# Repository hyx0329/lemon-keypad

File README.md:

# Lemon Keypad

> [English](README.md), [简体中文](README.zh.md)

A macro pad/mechanical keyboard based on RP2040. This is *probably* an *improved* version of the [original adafruit version](https://learn.adafruit.com/qtpy-lemon-mechanical-keypad-macropad/).

This is a simple 6-key keypad. What makes it different is that the main program is written in async Python(CircuitPython).
With python's flexibility, a lot can be done with ease with this keypad, on demand.

<!-- TOC depthfrom:2 -->

- [Project folders and their content](#project-folders-and-their-content)
- [Software implementation](#software-implementation)
    - [implemented](#implemented)
    - [potentials left to users](#potentials-left-to-users)
- [Hardware components](#hardware-components)
- [The real thing: close looks](#the-real-thing-close-looks)

<!-- /TOC -->

This repo consists of shell CAD(FreeCAD & STL), PCB design files(KiCAD), and software(CircuitPython project).

I found myself lack the capability/motivation to productize it, so I decided to publish it and hope it last longer, inspiring others.

## Project folders and their content

- CAD: stores CAD files for shell
- lemon-rp2040-keypad: kicad project file
- software: CircuitPython project directory

## Software implementation

### implemented

- keyboard keys input
    - including consumer control keys
- mouse input
- complex key actions
    - key combinations
    - key sequences
    - tap dance
    - layer switch
    - delay
- custom function
    - gyro mouse(built-in example)
    - level gauge(built-in example)

### potentials left to users

- random number generator
- Whack-a-Mole
- a BIG button used up-side-down
- password storage(with pin protection)
- ducky pad
- etc.

## Hardware components

- RP2040
- LSM6DS3TRC inertial module(gyro & accelerometer)
- WS2812 * 6
- MX switch hot-swappable socket
- Kailh BOX white switches
- WB25Q128JVSQ flash memory
- AMS1117-3V3
- misc passive components

## The real thing: close looks

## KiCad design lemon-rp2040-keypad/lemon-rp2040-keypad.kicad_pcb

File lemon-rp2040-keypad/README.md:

# Lemmon Keypad KiCAD Project

Have fun! :D It's just a prototype and design issues may exist, despite I did verify the design with the real thing.

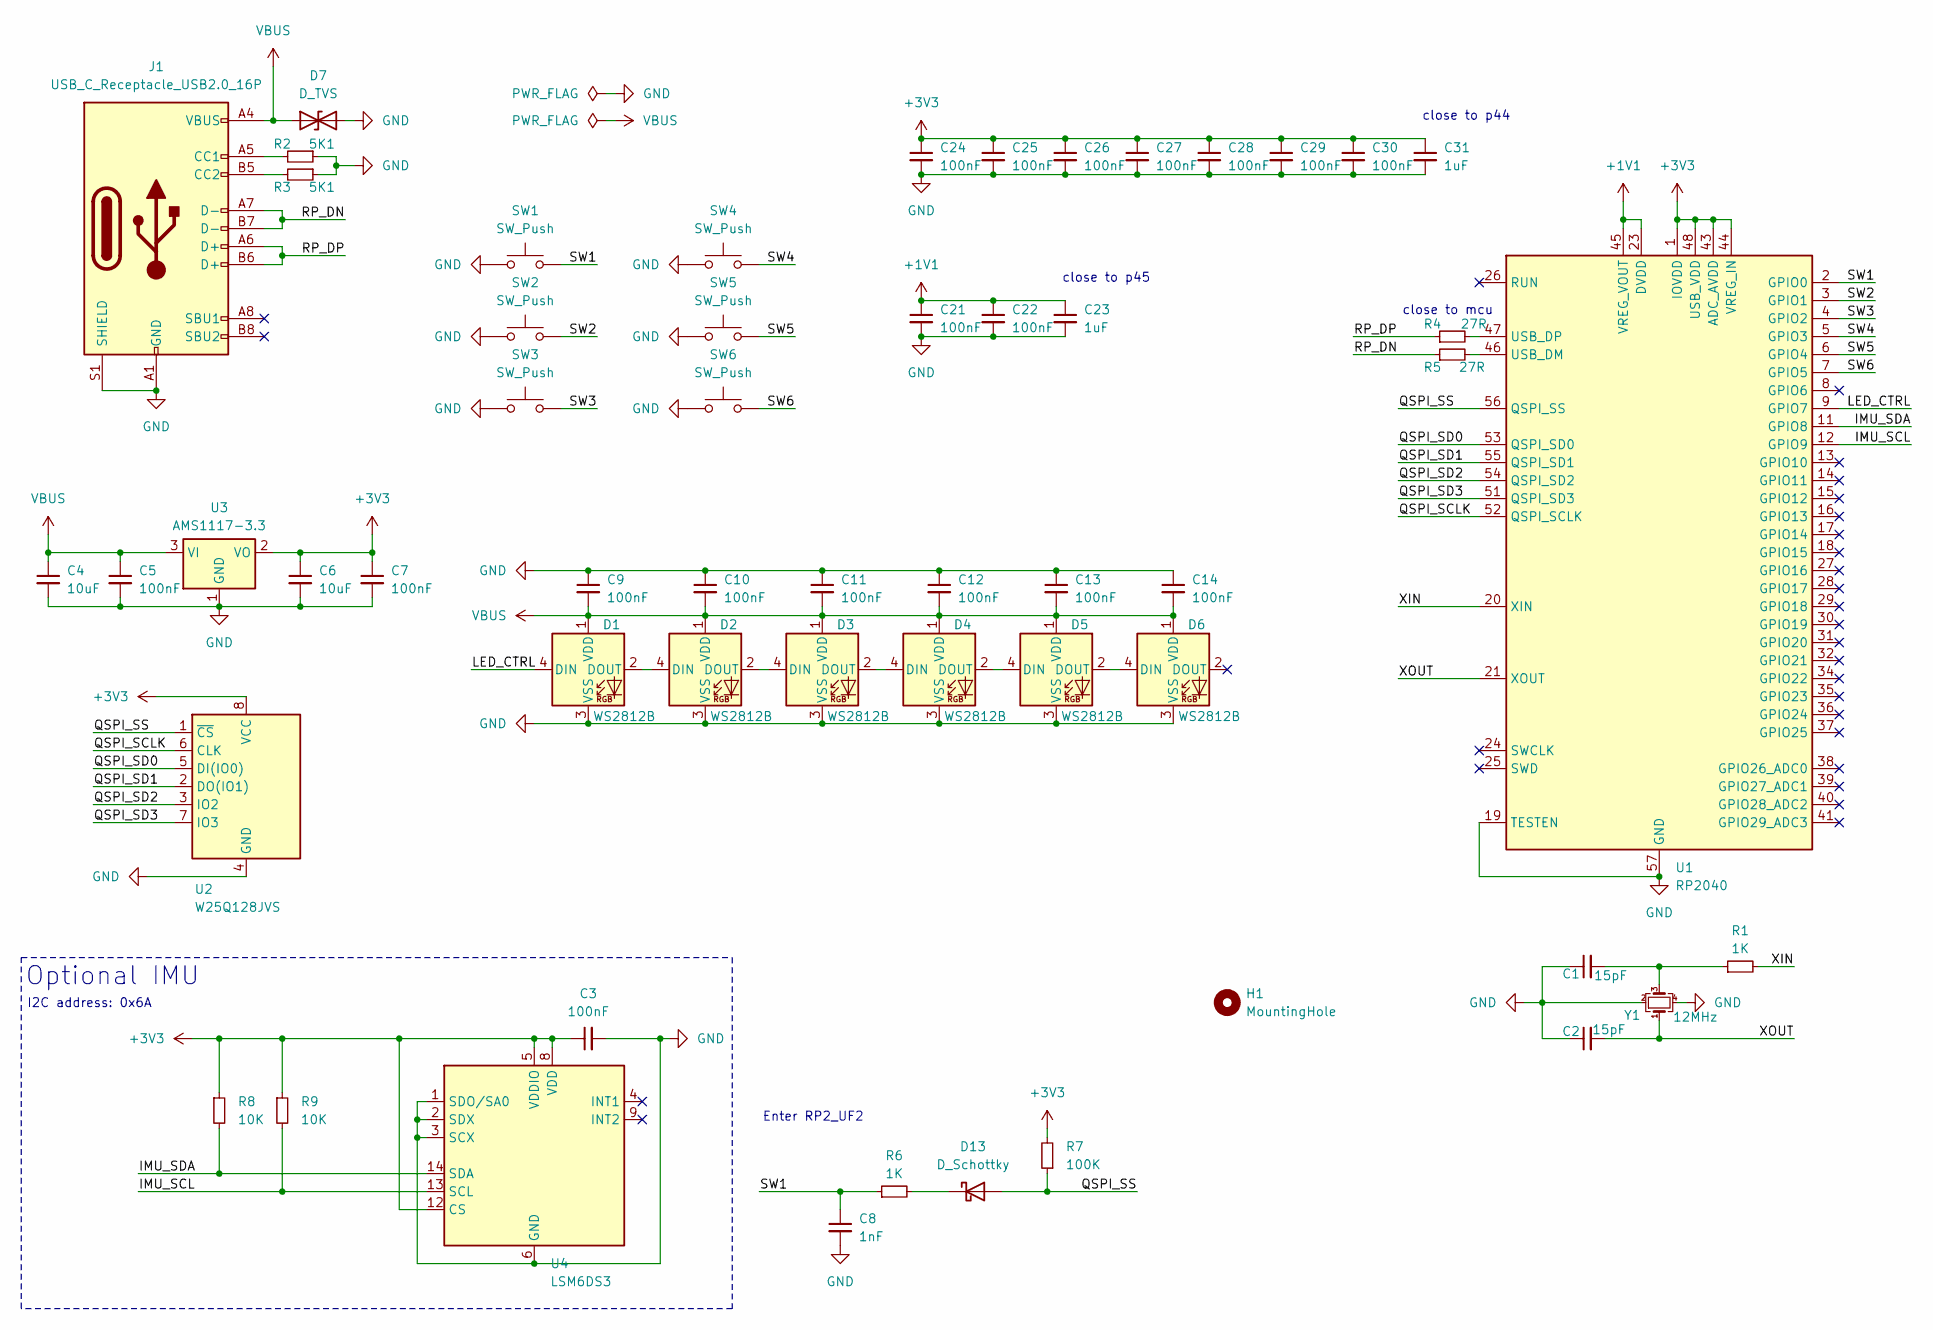
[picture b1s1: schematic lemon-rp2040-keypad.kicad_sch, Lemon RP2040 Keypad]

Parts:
C1, C2: 15pF; C_0402_1005Metric
C3, C5, C7, C9, C10, C11, C12, C13, C14, C21, C22, C24, C25, C26, C27, C28, C29, C30: 100nF; C_0402_1005Metric
C4, C6: 10uF; C_0603_1608Metric
C8: 1nF; C_0402_1005Metric
C23, C31: 1uF; C_0402_1005Metric
D1, D2, D3, D4, D5, D6: WS2812B; LED_WS2812B_PLCC4_5.0x5.0mm_P3.2mm
D7: D_TVS; D_SOD-323
D13: D_Schottky; D_SOD-323
H1: MountingHole; MountingHole_3.2mm_M3
J1: USB_C_Receptacle_USB2.0_16P; USB_C_Receptacle_G-Switch_GT-USB-7010ASV
R1, R6: 1K; R_0402_1005Metric
R2, R3: 5K1; R_0402_1005Metric
R4, R5: 27R; R_0402_1005Metric
R7: 100K; R_0402_1005Metric
R8, R9: 10K; R_0402_1005Metric
SW1, SW2, SW3, SW4, SW5, SW6: SW_Push; Kailh_socket_MX_optional
U1: RP2040; QFN-56-1EP_7x7mm_P0.4mm_EP3.2x3.2mm
U2: W25Q128JVS; SOIC-8_5.23x5.23mm_P1.27mm
U3: AMS1117-3.3; SOT-223-3_TabPin2
U4: LSM6DS3; LGA-14_3x2.5mm_P0.5mm_LayoutBorder3x4y
Y1: 12MHz; Crystal_SMD_3225-4Pin_3.2x2.5mm

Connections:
+1V1: C21.1, C22.1, C23.1, U1.23 (DVDD), U1.45 (VREG_VOUT), U1.50 (DVDD)
+3V3: C3.1, C6.1, C7.1, C24.1, C25.1, C26.1, C27.1, C28.1, C29.1, C30.1, C31.1, R7.2, R8.1, R9.1, U1.1 (IOVDD), U1.10 (IOVDD), U1.22 (IOVDD), U1.33 (IOVDD), U1.42 (IOVDD), U1.43 (ADC_AVDD), U1.44 (VREG_IN), U1.48 (USB_VDD), U1.49 (IOVDD), U2.8 (VCC), U3.2 (VO), U4.5 (VDDIO), U4.8 (VDD), U4.12 (CS)
/IMU_SCL: R9.2, U1.12 (GPIO9), U4.13 (SCL)
/IMU_SDA: R8.2, U1.11 (GPIO8), U4.14 (SDA)
/LED_CTRL: D1.4 (DIN), U1.9 (GPIO7)
/QSPI_SCLK: U1.52 (QSPI_SCLK), U2.6 (CLK)
/QSPI_SD0: U1.53 (QSPI_SD0), U2.5 (DI(IO0))
/QSPI_SD1: U1.55 (QSPI_SD1), U2.2 (DO(IO1))
/QSPI_SD2: U1.54 (QSPI_SD2), U2.3 (IO2)
/QSPI_SD3: U1.51 (QSPI_SD3), U2.7 (IO3)
/QSPI_SS: D13.2 (A), R7.1, U1.56 (QSPI_SS), U2.1 (~CS)
/RP_DN: J1.A7 (D-), J1.B7 (D-), R5.1
/RP_DP: J1.A6 (D+), J1.B6 (D+), R4.1
/SW1: C8.1, R6.1, SW1.1, U1.2 (GPIO0)
/SW2: SW2.2, U1.3 (GPIO1)
/SW3: SW3.2, U1.4 (GPIO2)
/SW4: SW4.2, U1.5 (GPIO3)
/SW5: SW5.2, U1.6 (GPIO4)
/SW6: SW6.2, U1.7 (GPIO5)
/XIN: R1.2, U1.20 (XIN)
/XOUT: C2.2, U1.21 (XOUT), Y1.1
GND: C1.1, C2.1, C3.2, C4.2, C5.2, C6.2, C7.2, C8.2, C9.1, C10.1, C11.1, C12.1, C13.1, C14.1, C21.2, C22.2, C23.2, C24.2, C25.2, C26.2, C27.2, C28.2, C29.2, C30.2, C31.2, D1.3 (VSS), D2.3 (VSS), D3.3 (VSS), D4.3 (VSS), D5.3 (VSS), D6.3 (VSS), D7.2 (A2), J1.A1 (GND), J1.A12 (GND), J1.B1 (GND), J1.B12 (GND), J1.S1 (SHIELD), R2.1, R3.1, SW1.2, SW2.1, SW3.1, SW4.1, SW5.1, SW6.1, U1.19 (TESTEN), U1.57 (GND), U2.4 (GND), U3.1 (GND), U4.1 (SDO/SA0), U4.2 (SDX), U4.3 (SCX), U4.6 (GND), U4.7 (GND), Y1.2, Y1.4
unnamed: C1.2, R1.1, Y1.3
unnamed: D1.2 (DOUT), D2.4 (DIN)
unnamed: D2.2 (DOUT), D3.4 (DIN)
unnamed: D3.2 (DOUT), D4.4 (DIN)
unnamed: D4.2 (DOUT), D5.4 (DIN)
unnamed: D5.2 (DOUT), D6.4 (DIN)
unnamed: D13.1 (K), R6.2
unnamed: J1.A5 (CC1), R2.2
unnamed: J1.B5 (CC2), R3.2
unnamed: R5.2, U1.46 (USB_DM)
unnamed: R4.2, U1.47 (USB_DP)
VBUS: C4.1, C5.1, C9.2, C10.2, C11.2, C12.2, C13.2, C14.2, D1.1 (VDD), D2.1 (VDD), D3.1 (VDD), D4.1 (VDD), D5.1 (VDD), D6.1 (VDD), D7.1 (A1), J1.A4 (VBUS), J1.A9 (VBUS), J1.B4 (VBUS), J1.B9 (VBUS), U3.3 (VI)

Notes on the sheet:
Enter RP2_UF2
close to mcu
I2C address: 0x6A
close to p45
Optional IMU
close to p44

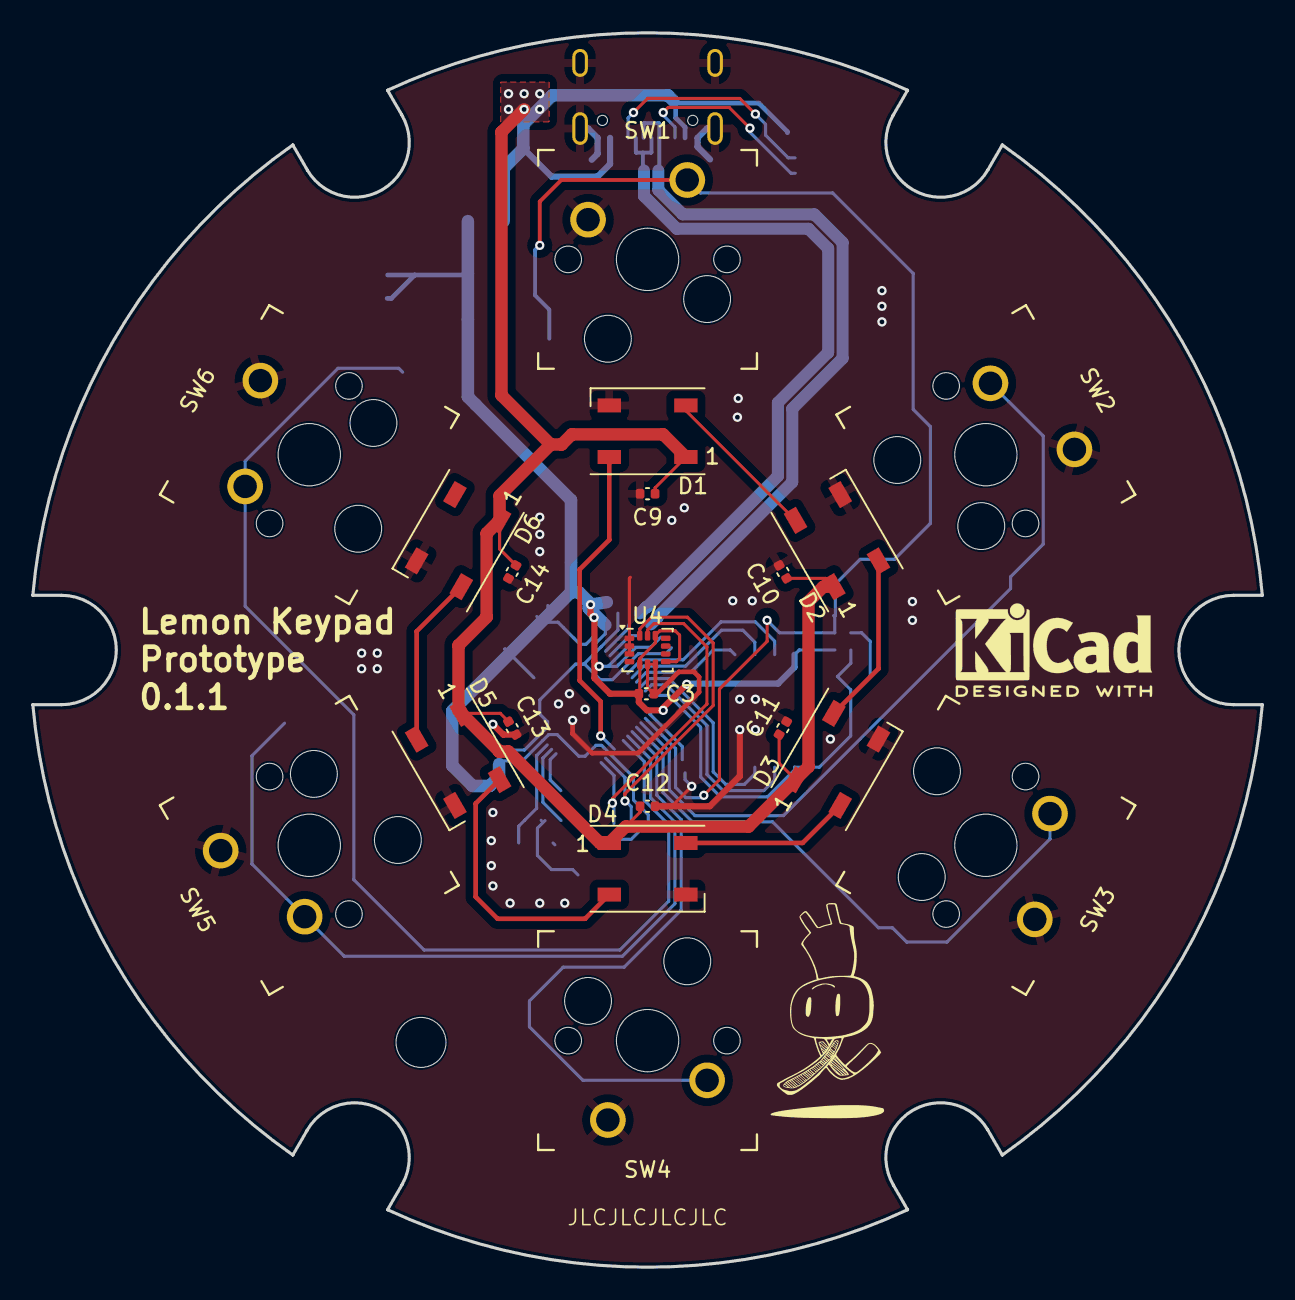
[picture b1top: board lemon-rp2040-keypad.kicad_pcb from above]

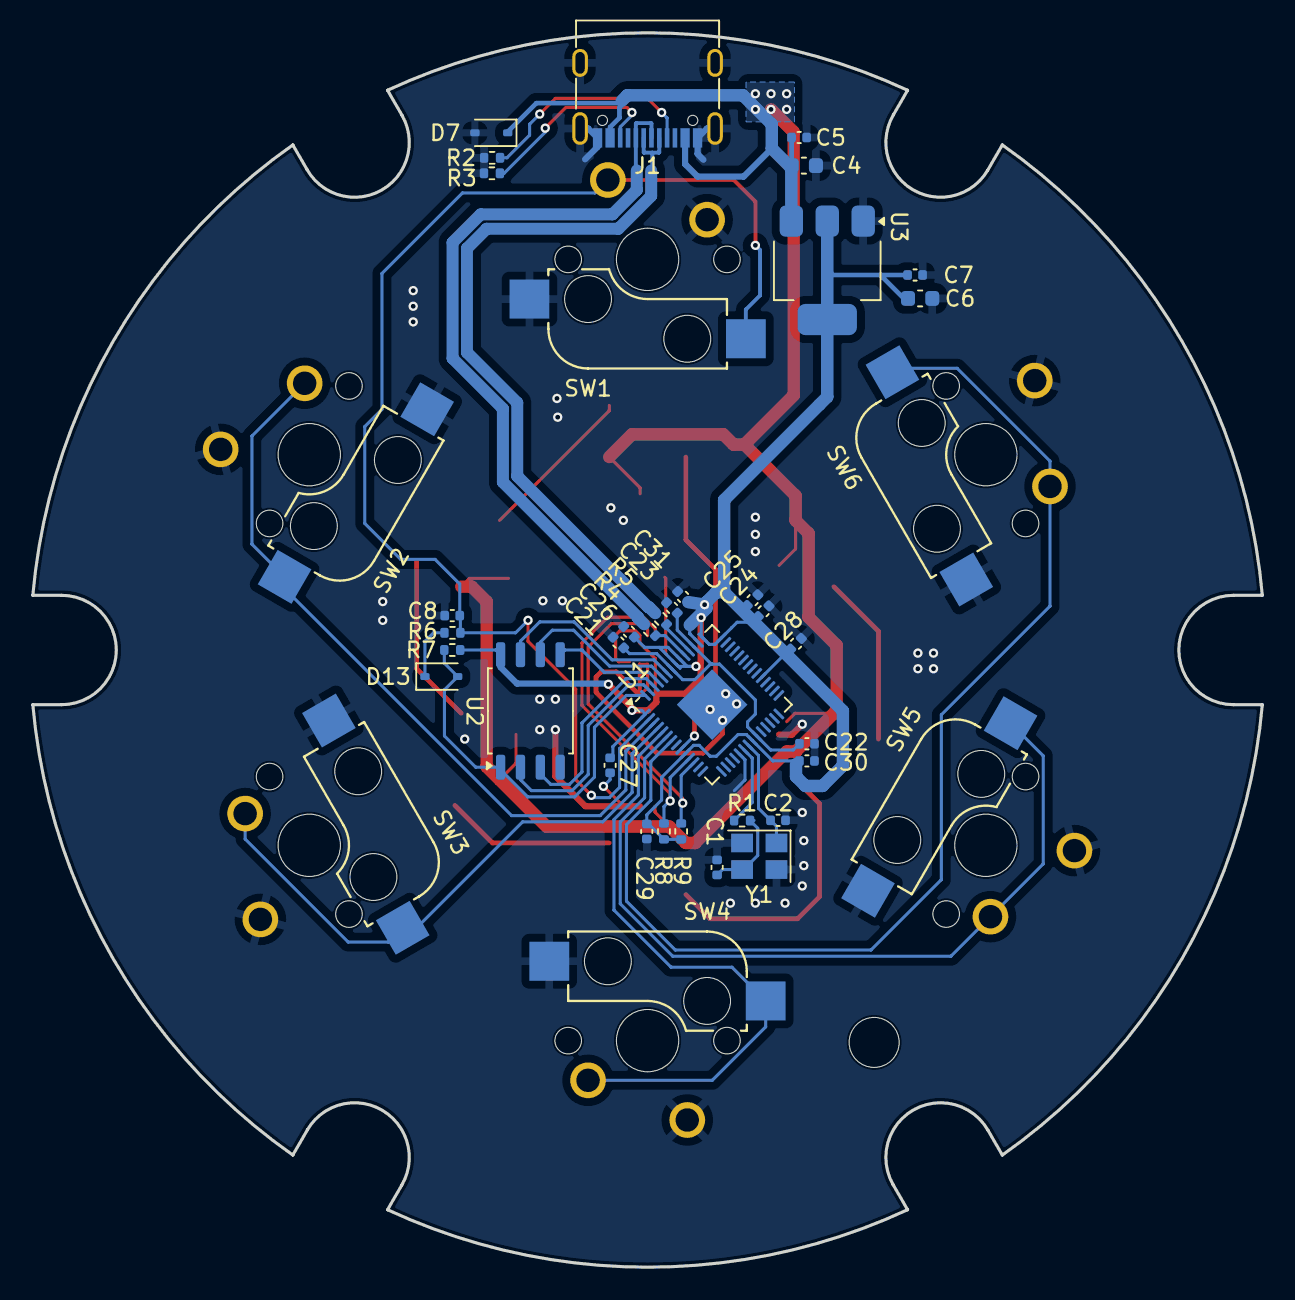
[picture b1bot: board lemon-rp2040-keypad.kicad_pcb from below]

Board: 2 copper layers, 78.7 x 79.0 mm, 55 parts (34 on the bottom side), 34 nets.

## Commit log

2024-09-23 public version
